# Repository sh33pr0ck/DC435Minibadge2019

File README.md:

# DC435Minibadge2019
 
Based on the minibadge by luke jenkins: https://github.com/lukejenkins/minibadge

Arduino code uses a tutorial I found on adafruit and edited to for the correct pinout. The LED is a common anode rgb.

Use the icsp pads with a programmer to load code to the attiny85.

I'll add the schematics etc. soon.

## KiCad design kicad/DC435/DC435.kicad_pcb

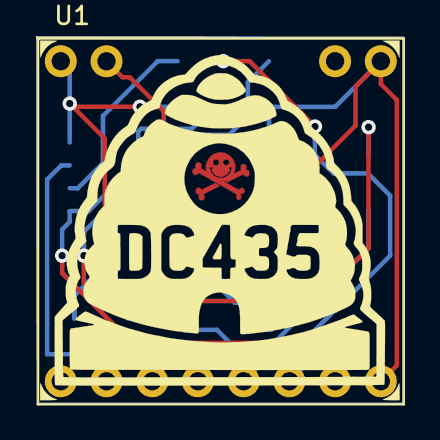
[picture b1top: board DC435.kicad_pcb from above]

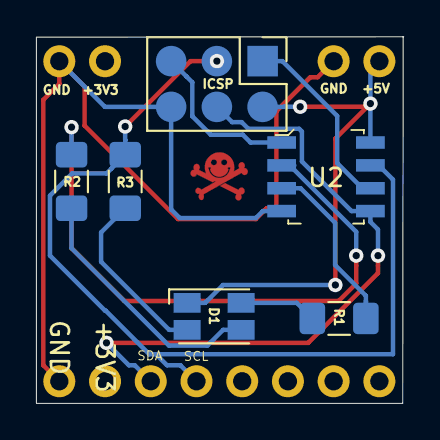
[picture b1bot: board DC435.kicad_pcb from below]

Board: 2 copper layers, 20.4 x 20.4 mm, 7 parts (6 on the bottom side), 12 nets.

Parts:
D1: LED_RABG; LED_Avago_PLCC4_3.2x2.8mm_CW
ICSP: AVR-ISP-6; PinHeader_2x03_P2.54mm_Vertical
R1, R2, R3: R_US; R_1206_3216Metric_Pad1.42x1.75mm_HandSolder
U1: SAINTCON-Minibadge
U2: ATTINY85-20SU; SOIC-8_W5.3mm

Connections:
+3V3: U1.7, U1.15
+5V: D1.2, ICSP.2, U1.1, U2.8
/PB0: ICSP.4, U1.14, U2.5
/PB2: ICSP.3, R3.2, U1.13, U2.7
/RST: ICSP.5, U2.1
GND: ICSP.6, U1.2, U1.8, U1.16, U2.4
unnamed: D1.1, R1.1
unnamed: D1.3, R3.1
unnamed: D1.4, R2.1
unnamed: ICSP.1, U2.6
unnamed: R1.2, U2.3
unnamed: R2.2, U2.2

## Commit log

2019-10-29 attiny code
    Added attiny code
2022-07-20 Added Kicad
